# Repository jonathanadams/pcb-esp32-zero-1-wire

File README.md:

# ESP32-Zero 1-Wire Sensor

This PCB for is designed for use with the 'ESP32 Zero' boards such as [Waveshare ESP32-C6-Zero](https://www.waveshare.com/wiki/ESP32-C6-Zero) or [Waveshare ESP32-C3-Zero](https://www.waveshare.com/wiki/ESP32-C3-Zero) and 1-Wire sensors. You can hook up any 1-Wire sensors but it was primarialy designed to be used with Dallas DS18B20 temperature sensors.

<div style="display: flex; justify-content: center; gap: 10px;">
   
</div>

## Features

- Footprint for soldering castelated EPS32-C6-Zero or ESP32-C3-Zero board
- 6x terminal block 1-Wire ports
- Mode select solder jumper for Normal/Paraside modes
- 42mm x 31mm borard

## Schematic

## Bill of Materials

| Ref   | Qty | Description/Value                    | Notes                          |
| ----- | --- | ------------------------------------ | ------------------------------ |
| U1    | 1   | ESP32-C3-Zero or ESP32-C6-Zero       |                                |
| U2-U7 | 6   | KF128 2.54mm Pitch 3P Screw Terminal |                                |
| R1    | 1   | 0805/2012 SMD Resistor (4.7k Ohm)    |                                |
| R2    | 1   | 0805/2012 SMD Resistor (75 Ohm)      | Check D1 LED Requirements      |
| D1    | 1   | 0805/2012 SMD LED                    | Check R2 Resistor Requirements |

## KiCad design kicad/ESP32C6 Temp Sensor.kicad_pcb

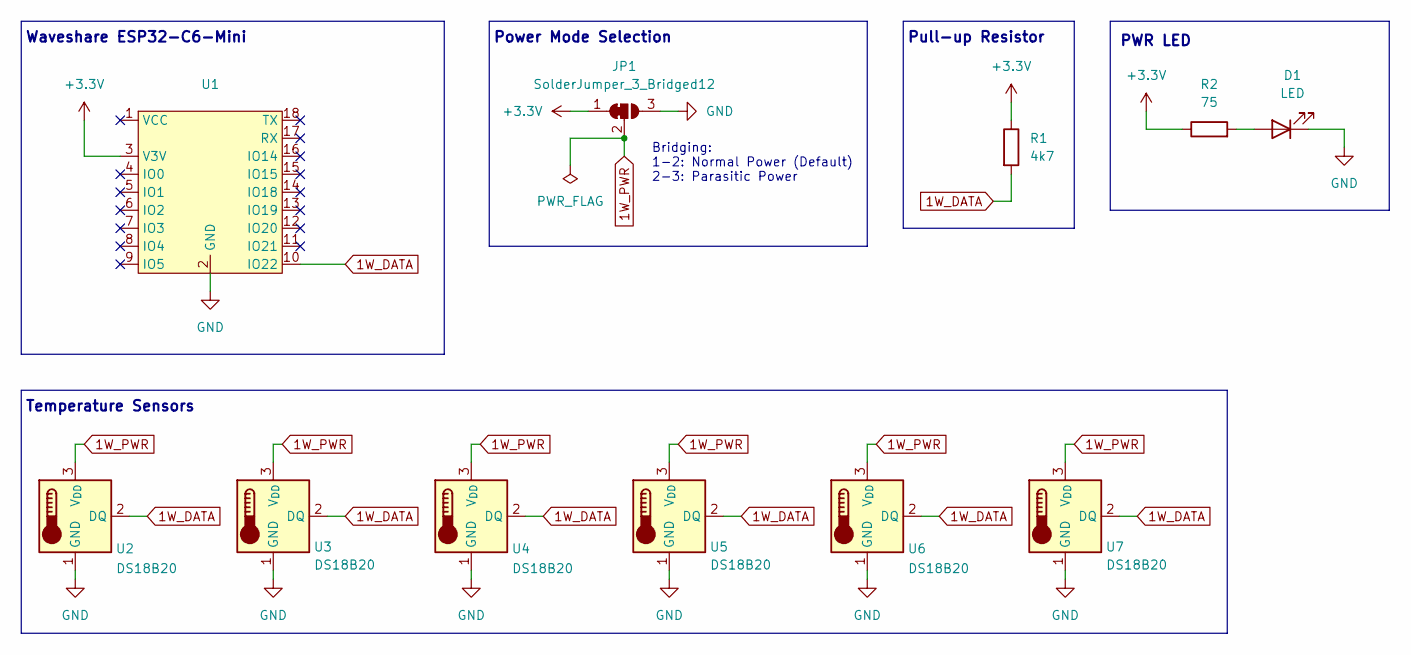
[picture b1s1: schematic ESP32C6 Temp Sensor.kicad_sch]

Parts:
D1: LED; LED_0805_2012Metric_Pad1.15x1.40mm_HandSolder
JP1: SolderJumper_3_Bridged12; SolderJumper-3_P1.3mm_Bridged12_Pad1.0x1.5mm_NumberLabels
R1: 4k7; R_0805_2012Metric_Pad1.20x1.40mm_HandSolder
R2: 75; R_0805_2012Metric_Pad1.20x1.40mm_HandSolder
U1: Waveshare-ESP32-C6-Zero
U2, U3, U4, U5, U6, U7: DS18B20; TerminalBlock_Xinya_XY308-2.54-3P_1x03_P2.54mm_Horizontal

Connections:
1W_DATA: R1.2, U1.10 (IO22), U2.2 (DQ), U3.2 (DQ), U4.2 (DQ), U5.2 (DQ), U6.2 (DQ), U7.2 (DQ)
1W_PWR: JP1.2 (C), U2.3 (V_{DD}), U3.3 (V_{DD}), U4.3 (V_{DD}), U5.3 (V_{DD}), U6.3 (V_{DD}), U7.3 (V_{DD})
+3.3V: JP1.1 (A), R1.1, R2.1, U1.3 (V3V)
GND: D1.1 (K), JP1.3 (B), U1.2 (GND), U2.1 (GND), U3.1 (GND), U4.1 (GND), U5.1 (GND), U6.1 (GND), U7.1 (GND)
unnamed: D1.2 (A), R2.2

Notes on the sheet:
Waveshare ESP32-C6-Mini
Pull-up Resistor
PWR LED
Power Mode Selection
Bridging: 1-2: Normal Power (Default) 2-3: Parasitic Power
Temperature Sensors

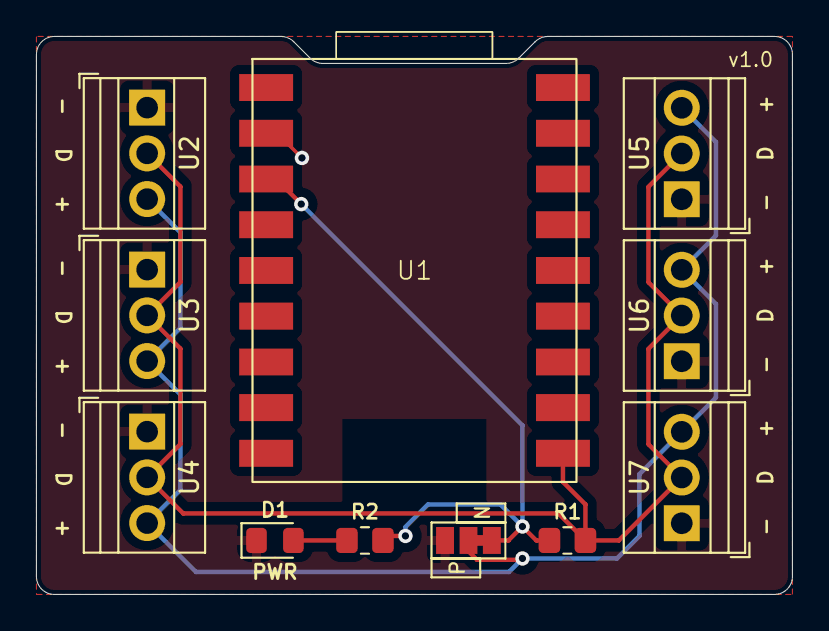
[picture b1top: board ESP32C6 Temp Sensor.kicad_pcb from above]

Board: 2 copper layers, 42.0 x 31.0 mm, 11 parts (0 on the bottom side), 5 nets.
